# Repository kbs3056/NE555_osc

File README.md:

# NE555_osc
NE555 oscillator with transistor output

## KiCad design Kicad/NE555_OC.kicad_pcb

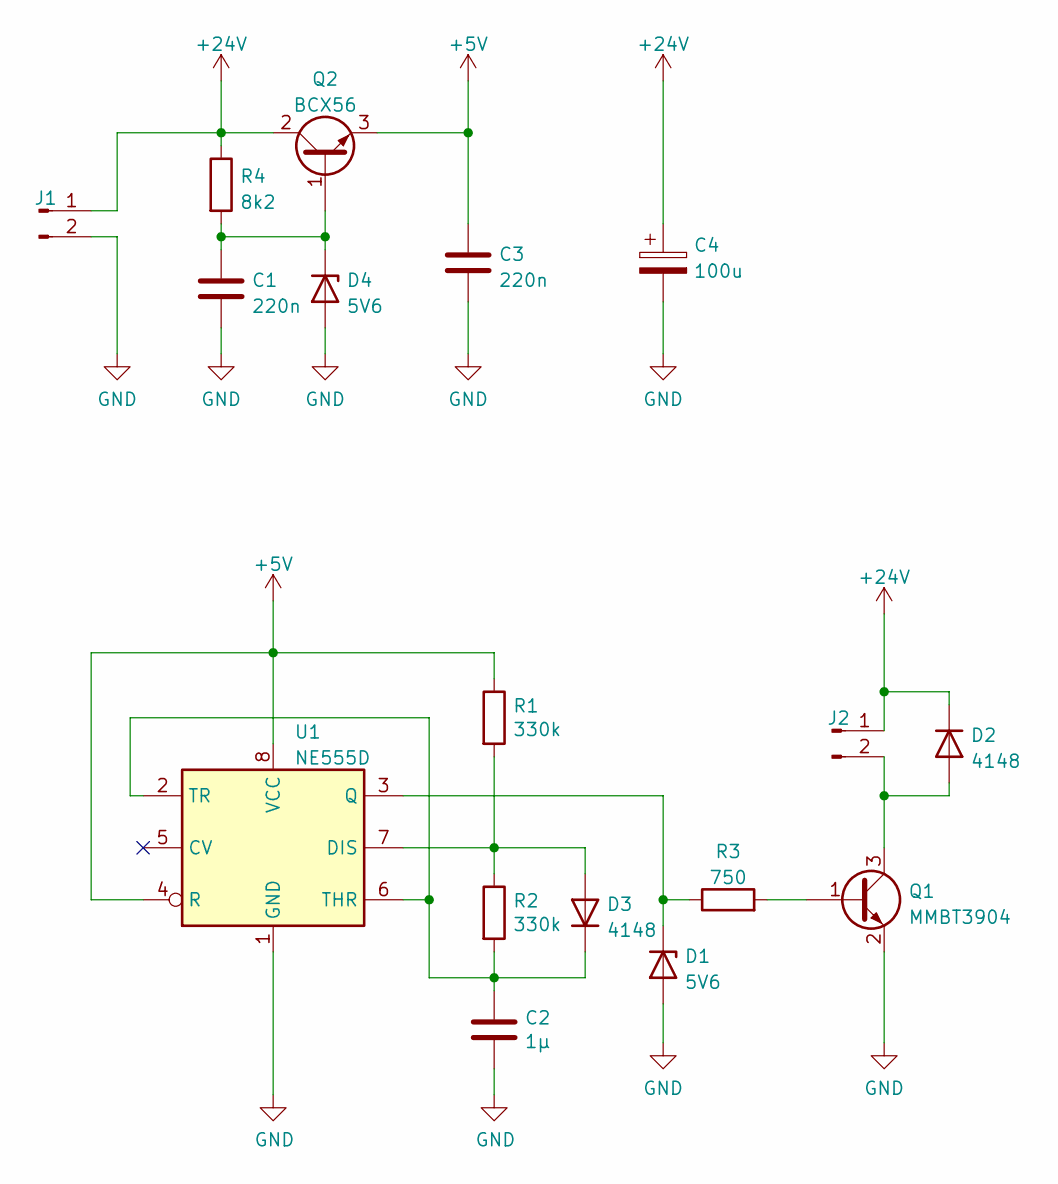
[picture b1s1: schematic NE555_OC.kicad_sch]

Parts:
C1, C3: 220n; C_0805_2012Metric
C2: 1µ; C_0805_2012Metric
C4: 100u; CP_Radial_D6.3mm_P2.50mm
D1, D4: 5V6; D_MiniMELF
D2, D3: 4148; D_MiniMELF
J1, J2: Conn_01x02_Male; PinHeader_1x02_P2.54mm_Vertical
Q1: MMBT3904; SOT-23
Q2: BCX56; SOT-89-3
R1, R2: 330k; R_1206_3216Metric
R3: 750; R_1206_3216Metric
R4: 8k2; R_1206_3216Metric
U1: NE555D; SOIC-8_3.9x4.9mm_P1.27mm

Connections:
+5V: C3.1, Q2.3 (E), R1.1, U1.4 (R), U1.8 (VCC)
+24V: C4.1, D2.1 (K), J1.1, J2.1, Q2.2 (C), R4.1
GND: C1.2, C2.2, C3.2, C4.2, D1.2 (A), D4.2 (A), J1.2, Q1.2 (E), U1.1 (GND)
unnamed: C1.1, D4.1 (K), Q2.1 (B), R4.2
unnamed: C2.1, D3.1 (K), R2.2, U1.2 (TR), U1.6 (THR)
unnamed: D1.1 (K), R3.1, U1.3 (Q)
unnamed: D2.2 (A), J2.2, Q1.3 (C)
unnamed: D3.2 (A), R1.2, R2.1, U1.7 (DIS)
unnamed: Q1.1 (B), R3.2

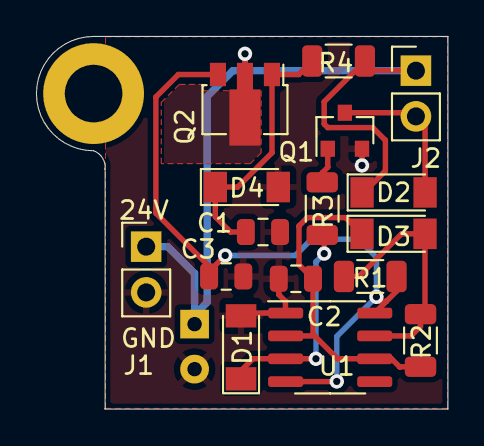
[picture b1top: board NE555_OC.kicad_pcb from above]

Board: 2 copper layers, 22.9 x 20.7 mm, 18 parts (1 on the bottom side), 9 nets.

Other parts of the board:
ref1: (no value)
